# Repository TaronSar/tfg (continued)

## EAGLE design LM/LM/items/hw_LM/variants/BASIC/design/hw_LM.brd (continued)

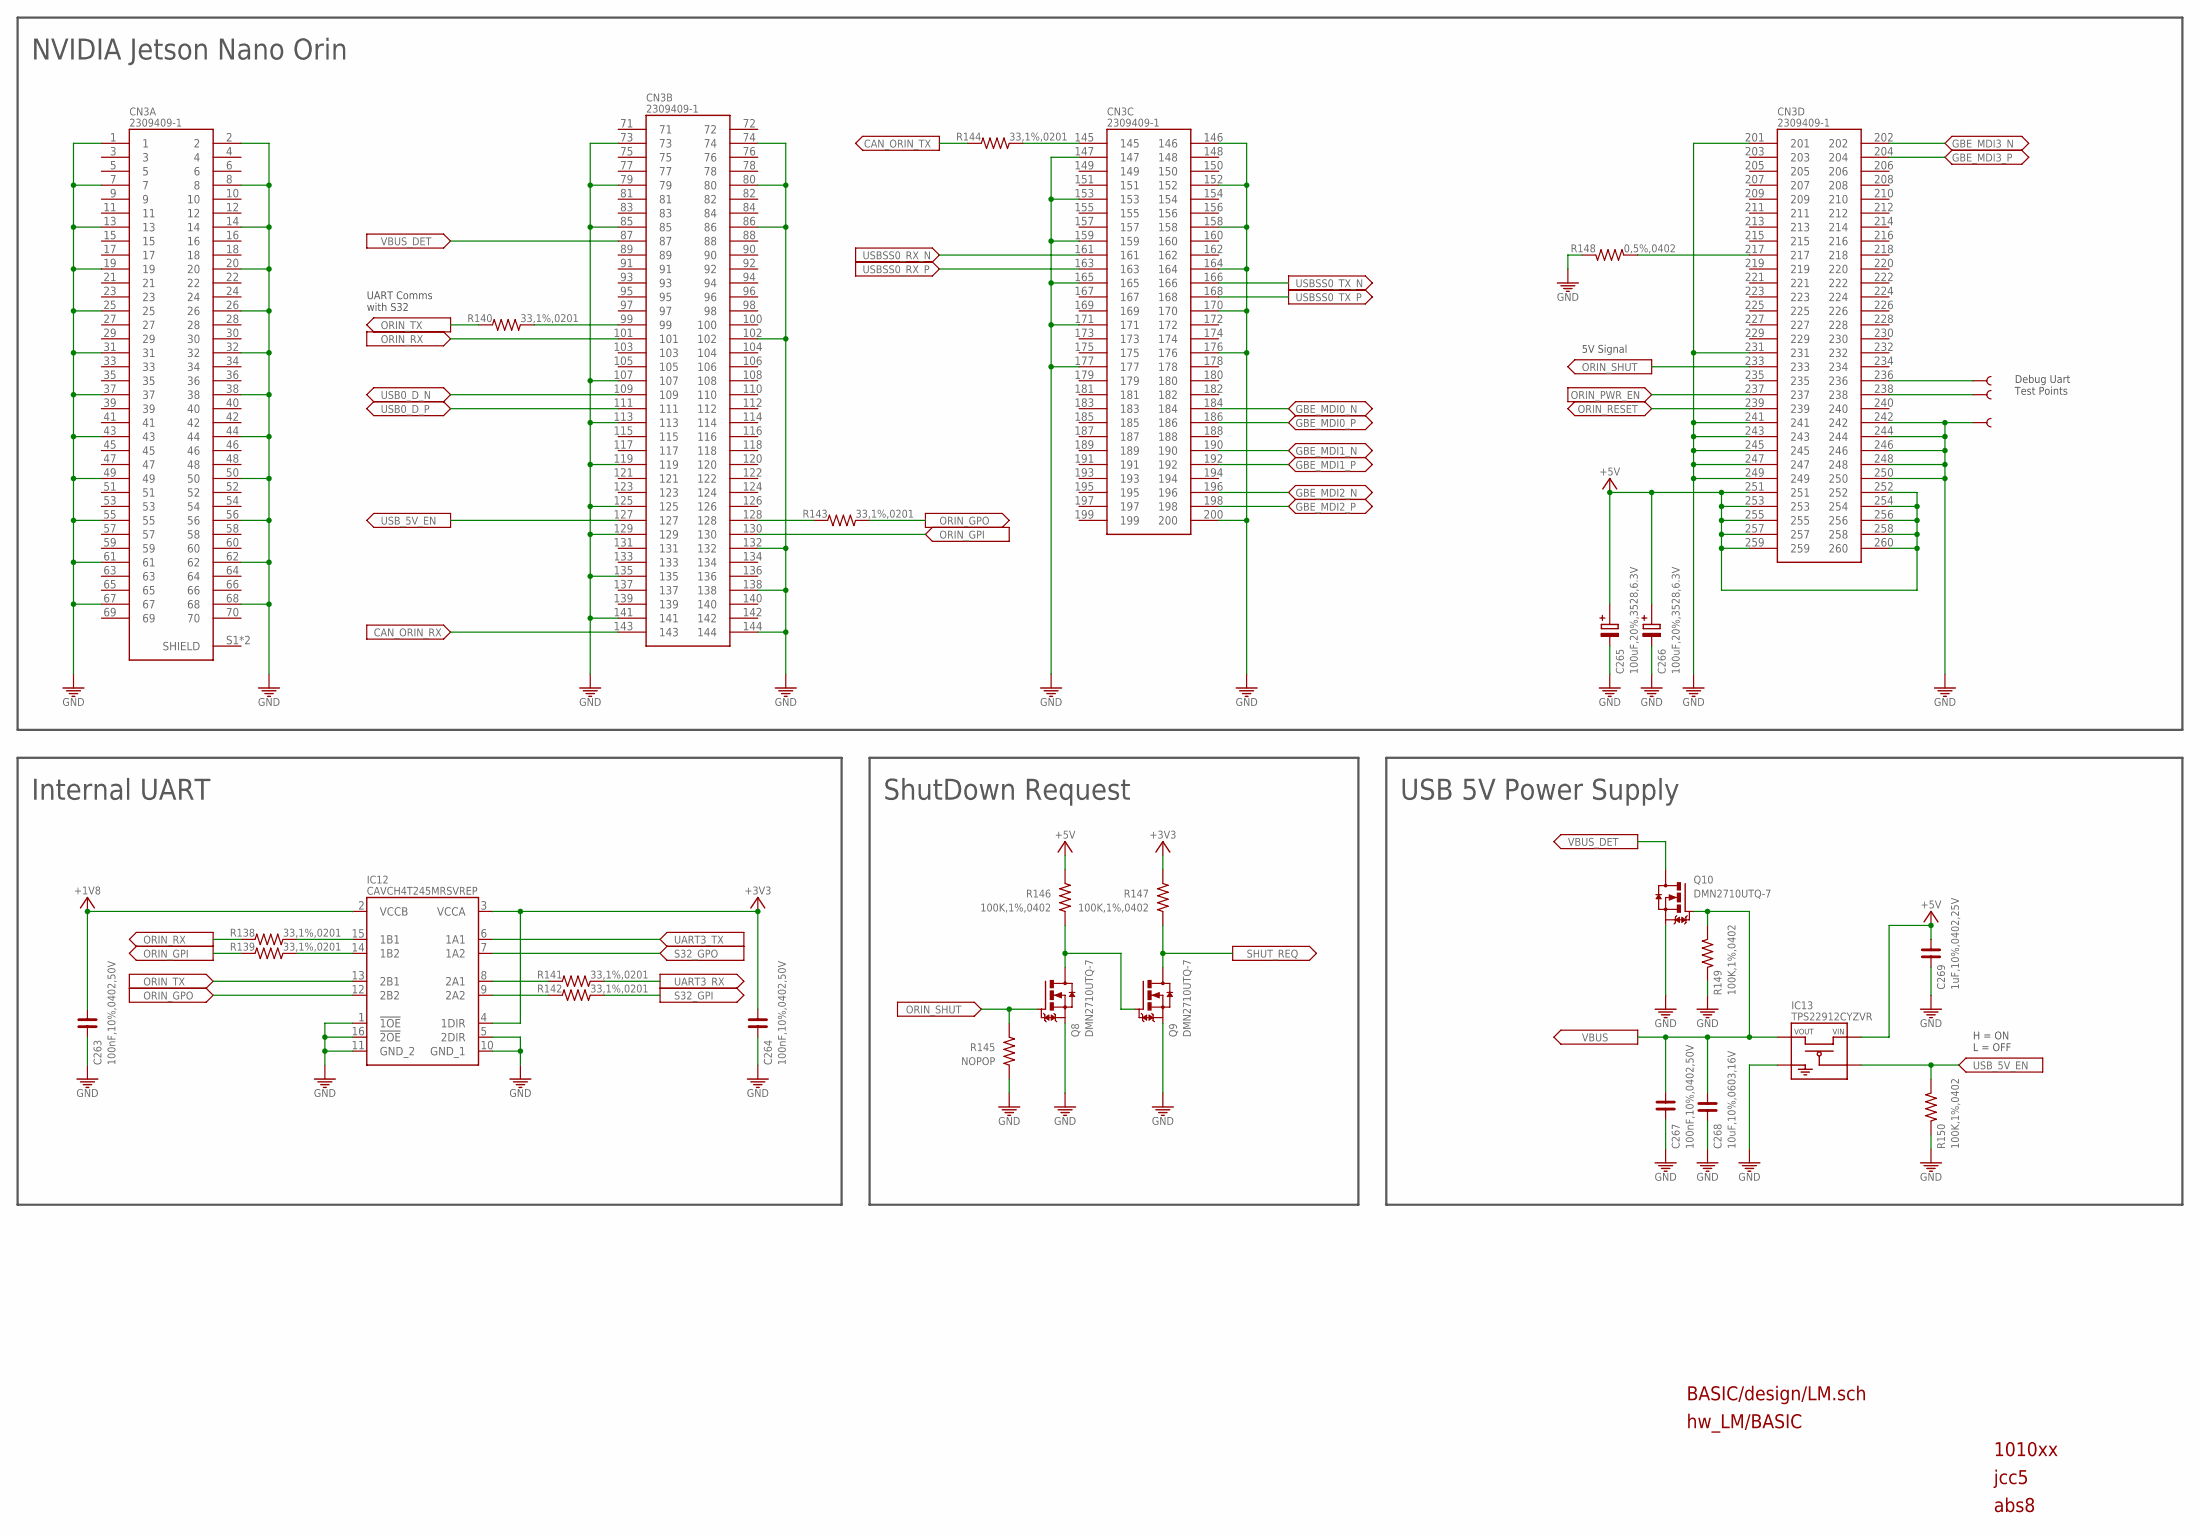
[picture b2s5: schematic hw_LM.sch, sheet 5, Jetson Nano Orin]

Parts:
C263, C264, C267: 100nF,10%,0402,50V; C0402
C265, C266: 100uF,20%,3528,6.3V; TE-B-3528
C268: 10uF,10%,0603,16V; C0603
C269: 1uF,10%,0402,25V; C0402
CN3: 2309409-1; TE_2309409-1
IC12: CAVCH4T245MRSVREP; UQFN-16
IC13: TPS22912CYZVR; DSBGA-4_YZV
Q8, Q9, Q10: DMN2710UTQ-7; SOT-523
R138, R139, R140, R141, R142, R143, R144: 33,1%,0201; R0201
R145: NOPOP; R0402
R146, R147, R149, R150: 100K,1%,0402; R0402
R148: 0,5%,0402; R0402
TP10, TP11, TP12: NOPOP; PAD.02X.02

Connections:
+1V8: C263.2, IC12.2 (VCCB); also elsewhere on the board
+3V3: C264.2, IC12.3 (VCCA), IC12.4 (1DIR), R147.1; also elsewhere on the board
+5V: C265.+, C266.+, C269.1, CN3.251, CN3.252, CN3.253, CN3.254, CN3.255, CN3.256, CN3.257, CN3.258, CN3.259, CN3.260, IC13.A2 (VIN), R146.1; also elsewhere on the board
CAN_ORIN_RX: CN3.143; also elsewhere on the board
CAN_ORIN_TX: R144.1; also elsewhere on the board
GBE_MDI0_N: CN3.184; also elsewhere on the board
GBE_MDI0_P: CN3.186; also elsewhere on the board
GBE_MDI1_N: CN3.190; also elsewhere on the board
GBE_MDI1_P: CN3.192; also elsewhere on the board
GBE_MDI2_N: CN3.196; also elsewhere on the board
GBE_MDI2_P: CN3.198; also elsewhere on the board
GBE_MDI3_N: CN3.202; also elsewhere on the board
GBE_MDI3_P: CN3.204; also elsewhere on the board
GND: C263.1, C264.1, C265.-, C266.-, C267.1, C268.1, C269.2, CN3.1, CN3.2, CN3.7, CN3.8, CN3.13, CN3.14, CN3.19, CN3.20, CN3.25, CN3.26, CN3.31, CN3.32, CN3.37, CN3.38, CN3.43, CN3.44, CN3.49, CN3.50, CN3.55, CN3.56, CN3.61, CN3.62, CN3.67, CN3.68, CN3.73, CN3.74, CN3.79, CN3.80, CN3.85, CN3.86, CN3.102, CN3.107, CN3.113, CN3.119, CN3.125, CN3.129, CN3.132, CN3.135, CN3.138, CN3.141, CN3.144, CN3.146, CN3.147, CN3.152, CN3.153, CN3.158, CN3.159, CN3.164, CN3.165, CN3.170, CN3.171, CN3.176, CN3.177, CN3.200, CN3.201, CN3.231, CN3.241, CN3.242, CN3.243, CN3.244, CN3.245, CN3.246, CN3.247, CN3.248, CN3.249, CN3.250, IC12.1 (!1OE), IC12.5 (2DIR), IC12.10 (GND_1), IC12.11 (GND_2), IC12.16 (!2OE), IC13.B1 (GND), Q8.2 (S), Q9.2 (S), Q10.2 (S), R145.2, R148.1, R149.2, R150.2, TP12.P$1; also elsewhere on the board
MODULE_ID: CN3.217, R148.2
unnamed: IC12.14 (1B2), R139.2
unnamed: Q8.3 (D), Q9.1 (G), R146.2
unnamed: IC12.15 (1B1), R138.2
unnamed: IC12.8 (2A1), R141.1
unnamed: IC12.9 (2A2), R142.1
ORINOUT: CN3.128, R143.1
ORIN_CAN_TX: CN3.145, R144.2
ORIN_GPI: CN3.130, R139.1
ORIN_GPO: IC12.12 (2B2), R143.2
ORIN_PWR_EN: CN3.237; also elsewhere on the board
ORIN_RESET: CN3.239; also elsewhere on the board
ORIN_RX: CN3.101, R138.1
ORIN_SHUT: CN3.233, Q8.1 (G), R145.1
ORIN_TX: IC12.13 (2B1), R140.1
ORIN_TXD: CN3.99, R140.2
S32_GPI: R142.2; also elsewhere on the board
S32_GPO: IC12.7 (1A2); also elsewhere on the board
SHUT_REQ: Q9.3 (D), R147.2; also elsewhere on the board
UART2_RXD: CN3.238, TP11.P$1
UART2_TXD: CN3.236, TP10.P$1
UART3_RX: R141.2; also elsewhere on the board
UART3_TX: IC12.6 (1A1); also elsewhere on the board
USB0_D_N: CN3.109; also elsewhere on the board
USB0_D_P: CN3.111; also elsewhere on the board
USBSS0_RX_N: CN3.161; also elsewhere on the board
USBSS0_RX_P: CN3.163; also elsewhere on the board
USBSS0_TX_N: CN3.166; also elsewhere on the board
USBSS0_TX_P: CN3.168; also elsewhere on the board
USB_5V_EN: CN3.127, IC13.B2 (ON), R150.1
VBUS: C267.2, C268.2, IC13.A1 (VOUT), Q10.1 (G), R149.1; also elsewhere on the board
VBUS_DET: CN3.87, Q10.3 (D)

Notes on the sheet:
NVIDIA Jetson Nano Orin
BASIC/design/LM.sch
hw_LM/BASIC
1010xx
jcc5
abs8
UART Comms with S32
Debug Uart Test Points
USB 5V Power Supply
5V Signal
ShutDown Request
Internal UART
H = ON L = OFF

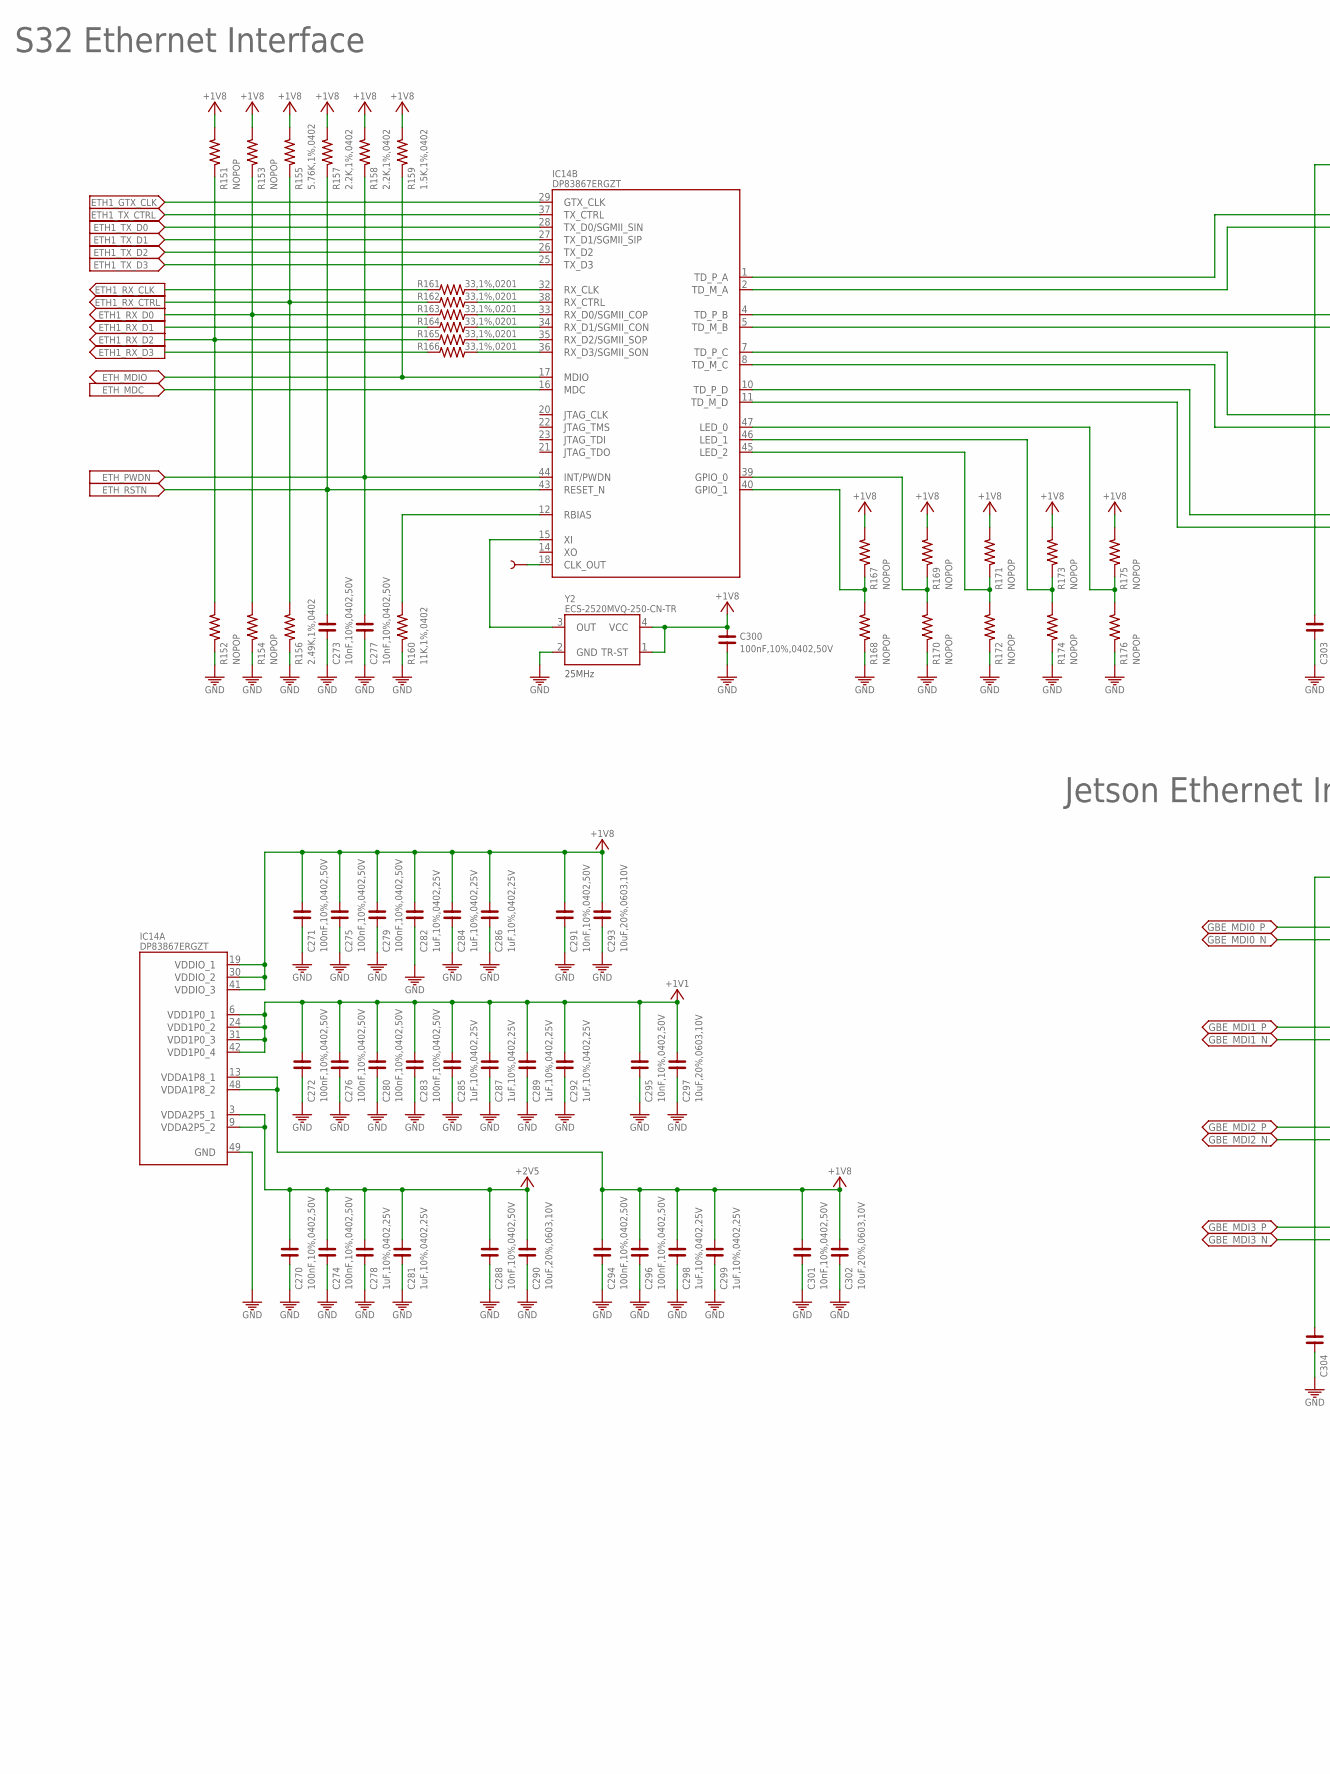
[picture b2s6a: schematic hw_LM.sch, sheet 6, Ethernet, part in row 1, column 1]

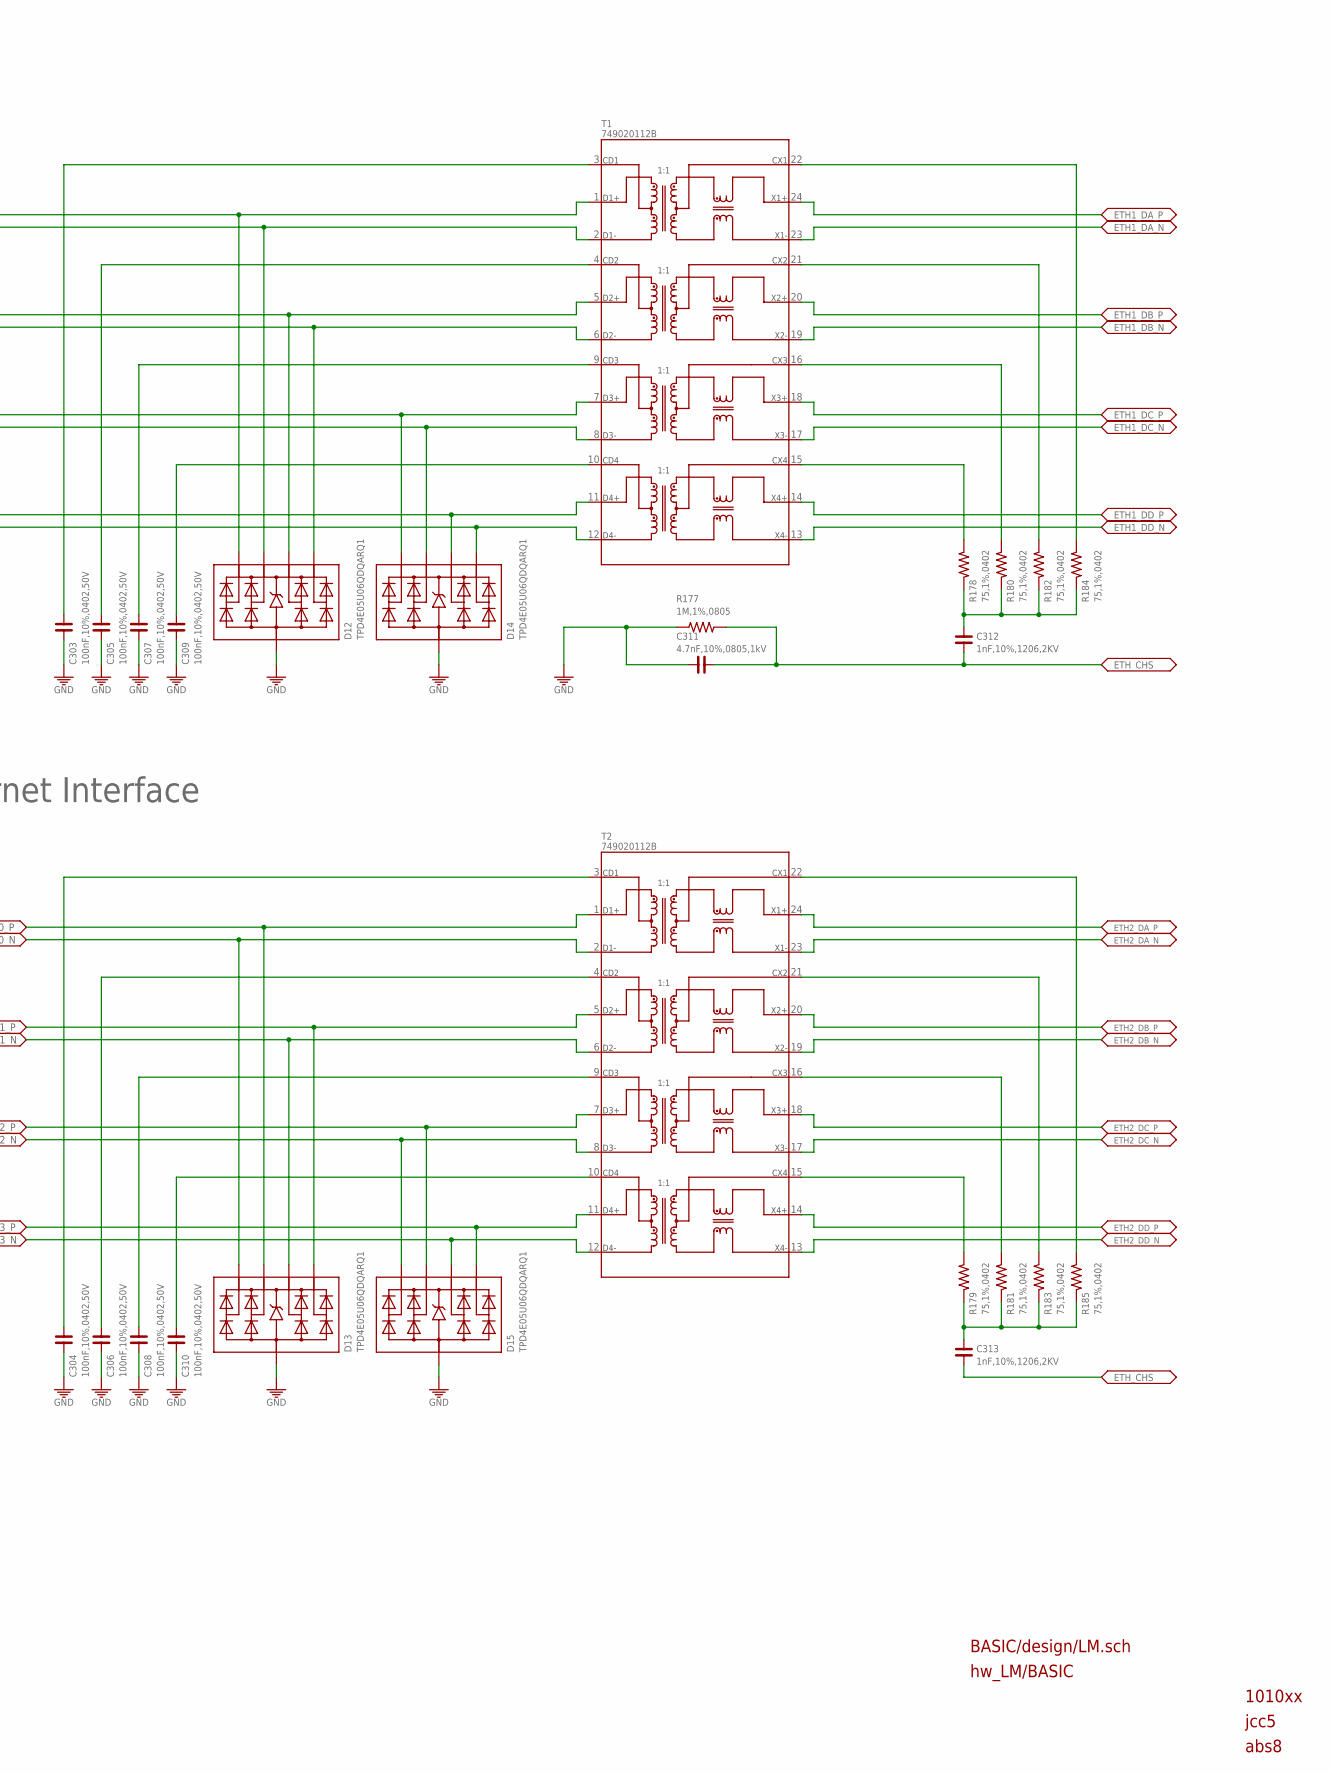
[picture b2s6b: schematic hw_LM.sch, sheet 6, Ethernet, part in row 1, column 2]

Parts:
C270, C271, C272, C274, C275, C276, C279, C280, C283, C294, C296, C300, C303, C304, C305, C306, C307, C308, C309, C310: 100nF,10%,0402,50V; C0402
C273, C277, C288, C291, C295, C301: 10nF,10%,0402,50V; C0402
C278, C281, C282, C284, C285, C286, C287, C289, C292, C298, C299: 1uF,10%,0402,25V; C0402
C290, C293, C297, C302: 10uF,20%,0603,10V; C0603
C311: 4.7nF,10%,0805,1kV; C0805
C312, C313: 1nF,10%,1206,2KV; C1206
D12, D13, D14, D15: TPD4E05U06QDQARQ1; DQA(R-PUSON-N10)
IC14: DP83867ERGZT; VQFN-48
R151, R152, R153, R154, R167, R168, R169, R170, R171, R172, R173, R174, R175, R176: NOPOP; R0402
R155: 5.76K,1%,0402; R0402
R156: 2.49K,1%,0402; R0402
R157, R158: 2.2K,1%,0402; R0402
R159: 1.5K,1%,0402; R0402
R160: 11K,1%,0402; R0402
R161, R162, R163, R164, R165, R166: 33,1%,0201; R0201
R177: 1M,1%,0805; R0805
R178, R179, R180, R181, R182, R183, R184, R185: 75,1%,0402; R0402
T1, T2: 749020112B
TP13: NOPOP; PAD.02X.02
Y2: ECS-2520MVQ-250-CN-TR; ECS-2520MVQ

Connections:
+1V1: C272.1, C276.1, C280.1, C283.1, C285.1, C287.1, C289.1, C292.1, C295.1, C297.1, IC14.6 (VDD1P0_1), IC14.24 (VDD1P0_2), IC14.31 (VDD1P0_3), IC14.42 (VDD1P0_4); also elsewhere on the board
+1V8: C271.1, C275.1, C279.1, C282.1, C284.1, C286.1, C291.1, C293.1, C294.1, C296.1, C298.1, C299.1, C300.1, C301.1, C302.1, IC14.13 (VDDA1P8_1), IC14.19 (VDDIO_1), IC14.30 (VDDIO_2), IC14.41 (VDDIO_3), IC14.48 (VDDA1P8_2), R151.2, R153.2, R155.2, R157.2, R158.2, R159.2, R167.2, R169.2, R171.2, R173.2, R175.2, Y2.1 (TR-ST), Y2.4 (VCC); also elsewhere on the board
+2V5: C270.1, C274.1, C278.1, C281.1, C288.1, C290.1, IC14.3 (VDDA2P5_1), IC14.9 (VDDA2P5_2); also elsewhere on the board
ETH1_DA_N: T1.23 (X1-); also elsewhere on the board
ETH1_DA_P: T1.24 (X1+); also elsewhere on the board
ETH1_DB_N: T1.19 (X2-); also elsewhere on the board
ETH1_DB_P: T1.20 (X2+); also elsewhere on the board
ETH1_DC_N: T1.17 (X3-); also elsewhere on the board
ETH1_DC_P: T1.18 (X3+); also elsewhere on the board
ETH1_DD_N: T1.13 (X4-); also elsewhere on the board
ETH1_DD_P: T1.14 (X4+); also elsewhere on the board
ETH1_GTX_CLK: IC14.29 (GTX_CLK); also elsewhere on the board
ETH1_MCT_A: R184.2, T1.22 (CX1)
ETH1_MCT_B: R182.2, T1.21 (CX2)
ETH1_MCT_C: R180.2, T1.16 (CX3)
ETH1_MCT_D: R178.2, T1.15 (CX4)
ETH1_RX_CLK: R161.1; also elsewhere on the board
ETH1_RX_CTRL: R155.1, R156.2, R162.1; also elsewhere on the board
ETH1_RX_D0: R153.1, R154.2, R163.1; also elsewhere on the board
ETH1_RX_D1: R164.1; also elsewhere on the board
ETH1_RX_D2: R151.1, R152.2, R165.1; also elsewhere on the board
ETH1_RX_D3: R166.1; also elsewhere on the board
ETH1_TCT_A: C303.1, T1.3 (CD1)
ETH1_TCT_B: C305.1, T1.4 (CD2)
ETH1_TCT_C: C307.1, T1.9 (CD3)
ETH1_TCT_D: C309.1, T1.10 (CD4)
ETH1_TD_A_N: D12.2 (K2), D12.9 (K2), IC14.2 (TD_M_A), T1.2 (D1-)
ETH1_TD_A_P: D12.1 (K1), D12.10 (K1), IC14.1 (TD_P_A), T1.1 (D1+)
ETH1_TD_B_N: D12.5 (K4), D12.6 (K4), IC14.5 (TD_M_B), T1.6 (D2-)
ETH1_TD_B_P: D12.4 (K3), D12.7 (K3), IC14.4 (TD_P_B), T1.5 (D2+)
ETH1_TD_C_N: D14.2 (K2), D14.9 (K2), IC14.8 (TD_M_C), T1.8 (D3-)
ETH1_TD_C_P: D14.1 (K1), D14.10 (K1), IC14.7 (TD_P_C), T1.7 (D3+)
ETH1_TD_D_N: D14.5 (K4), D14.6 (K4), IC14.11 (TD_M_D), T1.12 (D4-)
ETH1_TD_D_P: D14.4 (K3), D14.7 (K3), IC14.10 (TD_P_D), T1.11 (D4+)
ETH1_TX_CTRL: IC14.37 (TX_CTRL); also elsewhere on the board
ETH1_TX_D0: IC14.28 (TX_D0/SGMII_SIN); also elsewhere on the board
ETH1_TX_D1: IC14.27 (TX_D1/SGMII_SIP); also elsewhere on the board
ETH1_TX_D2: IC14.26 (TX_D2); also elsewhere on the board
ETH1_TX_D3: IC14.25 (TX_D3); also elsewhere on the board
ETH2_DA_N: T2.23 (X1-); also elsewhere on the board
ETH2_DA_P: T2.24 (X1+); also elsewhere on the board
ETH2_DB_N: T2.19 (X2-); also elsewhere on the board
ETH2_DB_P: T2.20 (X2+); also elsewhere on the board
ETH2_DC_N: T2.17 (X3-); also elsewhere on the board
ETH2_DC_P: T2.18 (X3+); also elsewhere on the board
ETH2_DD_N: T2.13 (X4-); also elsewhere on the board
ETH2_DD_P: T2.14 (X4+); also elsewhere on the board
ETH2_MCT_A: R185.2, T2.22 (CX1)
ETH2_MCT_B: R183.2, T2.21 (CX2)
ETH2_MCT_C: R181.2, T2.16 (CX3)
ETH2_MCT_D: R179.2, T2.15 (CX4)
ETH2_TCT_A: C304.1, T2.3 (CD1)
ETH2_TCT_B: C306.1, T2.4 (CD2)
ETH2_TCT_C: C308.1, T2.9 (CD3)
ETH2_TCT_D: C310.1, T2.10 (CD4)
ETH_CHS: C311.1, C312.2, C313.2, R177.1; also elsewhere on the board
ETH_CLK_OUT: IC14.18 (CLK_OUT), TP13.P$1
ETH_GPIO0: IC14.39 (GPIO_0), R169.1, R170.2
ETH_GPIO1: IC14.40 (GPIO_1), R167.1, R168.2
ETH_LED0: IC14.47 (LED_0), R175.1, R176.2
ETH_LED1: IC14.46 (LED_1), R173.1, R174.2
ETH_LED2: IC14.45 (LED_2), R171.1, R172.2
ETH_MDC: IC14.16 (MDC); also elsewhere on the board
ETH_MDIO: IC14.17 (MDIO), R159.1; also elsewhere on the board
ETH_PWDN: C277.1, IC14.44 (INT/PWDN), R158.1; also elsewhere on the board
ETH_RBIAS: IC14.12 (RBIAS), R160.1
ETH_RSTN: C273.1, IC14.43 (RESET_N), R157.1; also elsewhere on the board
ETH_XI: IC14.15 (XI), Y2.3 (OUT)
GBE_MDI0_N: D13.1 (K1), D13.10 (K1), T2.2 (D1-); also elsewhere on the board
GBE_MDI0_P: D13.2 (K2), D13.9 (K2), T2.1 (D1+); also elsewhere on the board
GBE_MDI1_N: D13.4 (K3), D13.7 (K3), T2.6 (D2-); also elsewhere on the board
GBE_MDI1_P: D13.5 (K4), D13.6 (K4), T2.5 (D2+); also elsewhere on the board
GBE_MDI2_N: D15.1 (K1), D15.10 (K1), T2.8 (D3-); also elsewhere on the board
GBE_MDI2_P: D15.2 (K2), D15.9 (K2), T2.7 (D3+); also elsewhere on the board
GBE_MDI3_N: D15.4 (K3), D15.7 (K3), T2.12 (D4-); also elsewhere on the board
GBE_MDI3_P: D15.5 (K4), D15.6 (K4), T2.11 (D4+); also elsewhere on the board
GND: C270.2, C271.2, C272.2, C273.2, C274.2, C275.2, C276.2, C277.2, C278.2, C279.2, C280.2, C281.2, C282.2, C283.2, C284.2, C285.2, C286.2, C287.2, C288.2, C289.2, C290.2, C291.2, C292.2, C293.2, C294.2, C295.2, C296.2, C297.2, C298.2, C299.2, C300.2, C301.2, C302.2, C303.2, C304.2, C305.2, C306.2, C307.2, C308.2, C309.2, C310.2, C311.2, D12.3 (CA), D12.8 (CA), D13.3 (CA), D13.8 (CA), D14.3 (CA), D14.8 (CA), D15.3 (CA), D15.8 (CA), IC14.49 (GND), R152.1, R154.1, R156.1, R160.2, R168.1, R170.1, R172.1, R174.1, R176.1, R177.2, Y2.2 (GND); also elsewhere on the board
unnamed: C312.1, R178.1, R180.1, R182.1, R184.1
unnamed: C313.1, R179.1, R181.1, R183.1, R185.1
RX_CLK: IC14.32 (RX_CLK), R161.2
RX_CTRL: IC14.38 (RX_CTRL), R162.2
RX_D0: IC14.33 (RX_D0/SGMII_COP), R163.2
RX_D1: IC14.34 (RX_D1/SGMII_CON), R164.2
RX_D2: IC14.35 (RX_D2/SGMII_SOP), R165.2
RX_D3: IC14.36 (RX_D3/SGMII_SON), R166.2

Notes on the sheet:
S32 Ethernet Interface
Jetson Ethernet Interface
25MHz
BASIC/design/LM.sch
hw_LM/BASIC
1010xx
jcc5
abs8

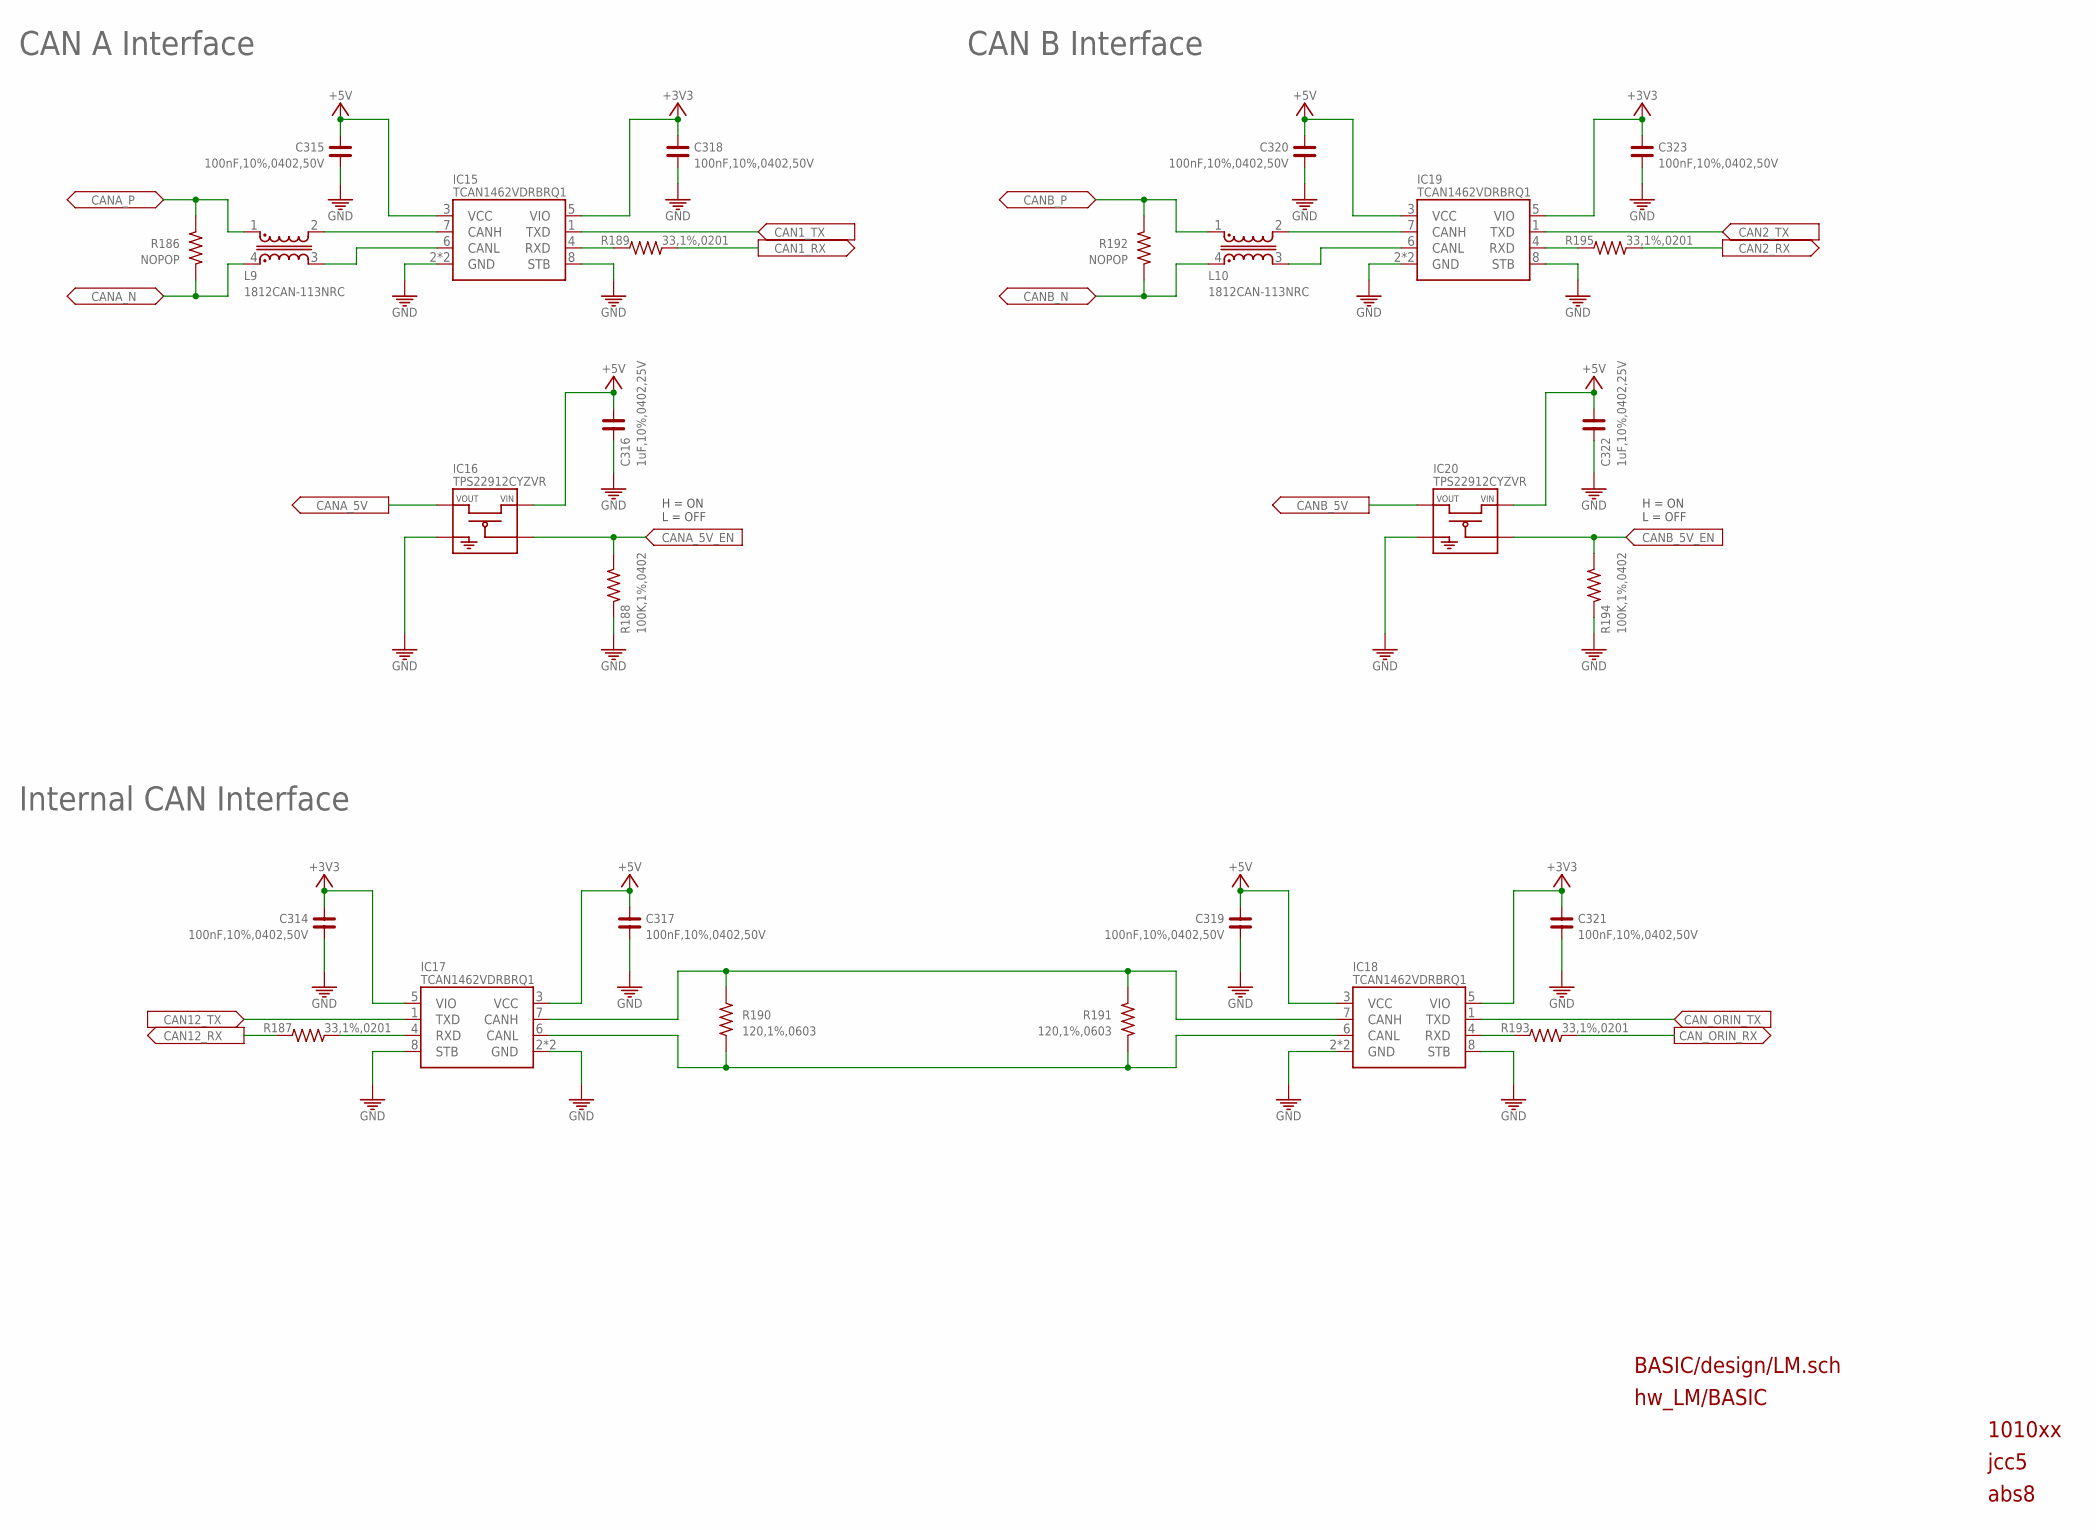
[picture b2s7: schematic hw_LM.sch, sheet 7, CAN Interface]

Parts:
C314, C315, C317, C318, C319, C320, C321, C323: 100nF,10%,0402,50V; C0402
C316, C322: 1uF,10%,0402,25V; C0402
IC15, IC17, IC18, IC19: TCAN1462VDRBRQ1; VSON-8
IC16, IC20: TPS22912CYZVR; DSBGA-4_YZV
L9, L10: 1812CAN-113NRC; 1812CAN
R186, R192: NOPOP; R0603
R187, R189, R193, R195: 33,1%,0201; R0201
R188, R194: 100K,1%,0402; R0402
R190, R191: 120,1%,0603; R0603

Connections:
+3V3: C314.2, C318.2, C321.2, C323.2, IC15.5 (VIO), IC17.5 (VIO), IC18.5 (VIO), IC19.5 (VIO); also elsewhere on the board
+5V: C315.2, C316.1, C317.2, C319.2, C320.2, C322.1, IC15.3 (VCC), IC16.A2 (VIN), IC17.3 (VCC), IC18.3 (VCC), IC19.3 (VCC), IC20.A2 (VIN); also elsewhere on the board
CAN1_N: IC15.6 (CANL), L9.3
CAN1_P: IC15.7 (CANH), L9.2
CAN1_RX: R189.2; also elsewhere on the board
CAN1_TX: IC15.1 (TXD); also elsewhere on the board
CAN2_N: IC19.6 (CANL), L10.3
CAN2_P: IC19.7 (CANH), L10.2
CAN2_RX: R195.2; also elsewhere on the board
CAN2_TX: IC19.1 (TXD); also elsewhere on the board
CAN12_RX: R187.1; also elsewhere on the board
CAN12_TX: IC17.1 (TXD); also elsewhere on the board
CANA_5V: IC16.A1 (VOUT); also elsewhere on the board
CANA_5V_EN: IC16.B2 (ON), R188.1; also elsewhere on the board
CANA_N: L9.4, R186.1; also elsewhere on the board
CANA_P: L9.1, R186.2; also elsewhere on the board
CANB_5V: IC20.A1 (VOUT); also elsewhere on the board
CANB_5V_EN: IC20.B2 (ON), R194.1; also elsewhere on the board
CANB_N: L10.4, R192.1; also elsewhere on the board
CANB_P: L10.1, R192.2; also elsewhere on the board
CAN_INT_N: IC17.6 (CANL), IC18.6 (CANL), R190.1, R191.1
CAN_INT_P: IC17.7 (CANH), IC18.7 (CANH), R190.2, R191.2
CAN_ORIN_RX: R193.2; also elsewhere on the board
CAN_ORIN_TX: IC18.1 (TXD); also elsewhere on the board
GND: C314.1, C315.1, C316.2, C317.1, C318.1, C319.1, C320.1, C321.1, C322.2, C323.1, IC15.2 (GND), IC15.8 (STB), IC15.9 (GND), IC16.B1 (GND), IC17.2 (GND), IC17.8 (STB), IC17.9 (GND), IC18.2 (GND), IC18.8 (STB), IC18.9 (GND), IC19.2 (GND), IC19.8 (STB), IC19.9 (GND), IC20.B1 (GND), R188.2, R194.2; also elsewhere on the board
unnamed: IC18.4 (RXD), R193.1
unnamed: IC17.4 (RXD), R187.2
unnamed: IC15.4 (RXD), R189.1
unnamed: IC19.4 (RXD), R195.1

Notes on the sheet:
CAN A Interface
Internal CAN Interface
CAN B Interface
BASIC/design/LM.sch
hw_LM/BASIC
1010xx
jcc5
abs8
H = ON L = OFF
